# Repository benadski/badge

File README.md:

# Fri3d Camp Badge

Elk zichzelf respecterend hacker/maker/DIY kamp, _moet_ een eigen badge hebben. Zo ook Fri3d Camp :-)

## Concept

Bij het ontwerp van de badge voor Fri3d Camp zijn we vertrokken van drie principes:

1. Een hoge _hack_-baarheid.
2. Leerzaam voor beginners.
3. Interactief.

Daarom brengt de badge het Arduino platform samen met infra-rode stralen om een eenvoudig Fri3d Camp draadloos (IR) netwerk te maken.

Het Arduino platform laat iedereen toe om de software van de badge aan te passen, of er iets totaal anders mee te doen. Naast de badge-functie voor Fri3d Camp, brengen we alle andere mogelijke functionaliteit van de microcontroller naar buiten, zodat de badge, na het kamp, letterlijk kan dienen als jouw eigen Arduino ontwikkel-bord.

Aan de hand van de IR componenten en bijhorende software kunnen de elementaire aspecten van draadloze communicatie uitgelegd worden.

### Meta-Leerzaam

Dit ontwerp is mijn eerste SMD-gebaseerde project en het is op zich al een leerzame ervaring. Daarom bevat deze repository tevens een [design dagboek](design/dagboek.md) waarin ik alle stappen van het proces beschrijf.

## Hardware Design

Twee bestaande projecten kunnen beschouwd worden als de spreekwoordelijke ouders van de badge: 

* [Arduino Pro Micro - 3.3V/8MHz van Sparkfun](https://www.sparkfun.com/products/12587)
* [TV B Gone van Mitch Altman](https://cornfieldelectronics.com/tvbgone/tvbg.home.php)

Voeg nog een IR receiver en een RGB LED toe en je hebt alle basis componenten voor een leerzame, interactieve en zeer _hack_-bare Fri3d Camp badge!

## Software

Om zelf aan de slag te gaan met de [software](src/README.md) zo eenvoudig mogelijk te maken, was één van dé belangrijkste aspecten een makkelijke integratie met het Arduino software platform. De mogelijkheid om de badge te programmeren via de Arduino IDE door middel van louter een micro-USB kabel was daarom een noodzaak.

Om het Arduino platform nog verder zo veel mogelijk te gebruiken, hebben we ook gekozen om zo dicht mogelijk bij een bestaand Arduino bord te blijven en zo is de badge in essentie een [Arduino Mirco](https://www.arduino.cc/en/Main/ArduinoBoardMicro) geworden.

Je kan dus onmiddellijk aan de slag, zoals met elke andere Arduino. Daarnaast bevat deze [repository](src/README.md) enkele applicaties specifiek geschreven voor de Fri3d Camp badge, en dit naast een bibliotheek die het aanspreken van de extras makkelijk maakt. Zo vindt je (weldra) hier:

* dé Fri3d Camp 2016 app
* een implementatie van de TV B Gone applicatie van Mitch Altman
* ...

Als je zelf een nieuwe app maakt die op de Fri3d Camp badge werkt en op een andere, leuke manier gebruik maakt van de IR communicatie en de RGB LED of van andere componenten die je er zelf aan toegevoegd hebt, bezorg ons dan deze code en we voegen ze toe aan deze repository (pull request).

## Credits

De badge werd ontworpen door Christophe VG, samen met de hele Fri3d Camp organisatie, en uitgewerkt met de hulp van Dragan Subotic, Yannick Verbelen, Maarten Weyn, Willy De a Court, Anthony Liekens, Dries Deroeck, Jef Van Den Broeck, Toon Van de Putte,...

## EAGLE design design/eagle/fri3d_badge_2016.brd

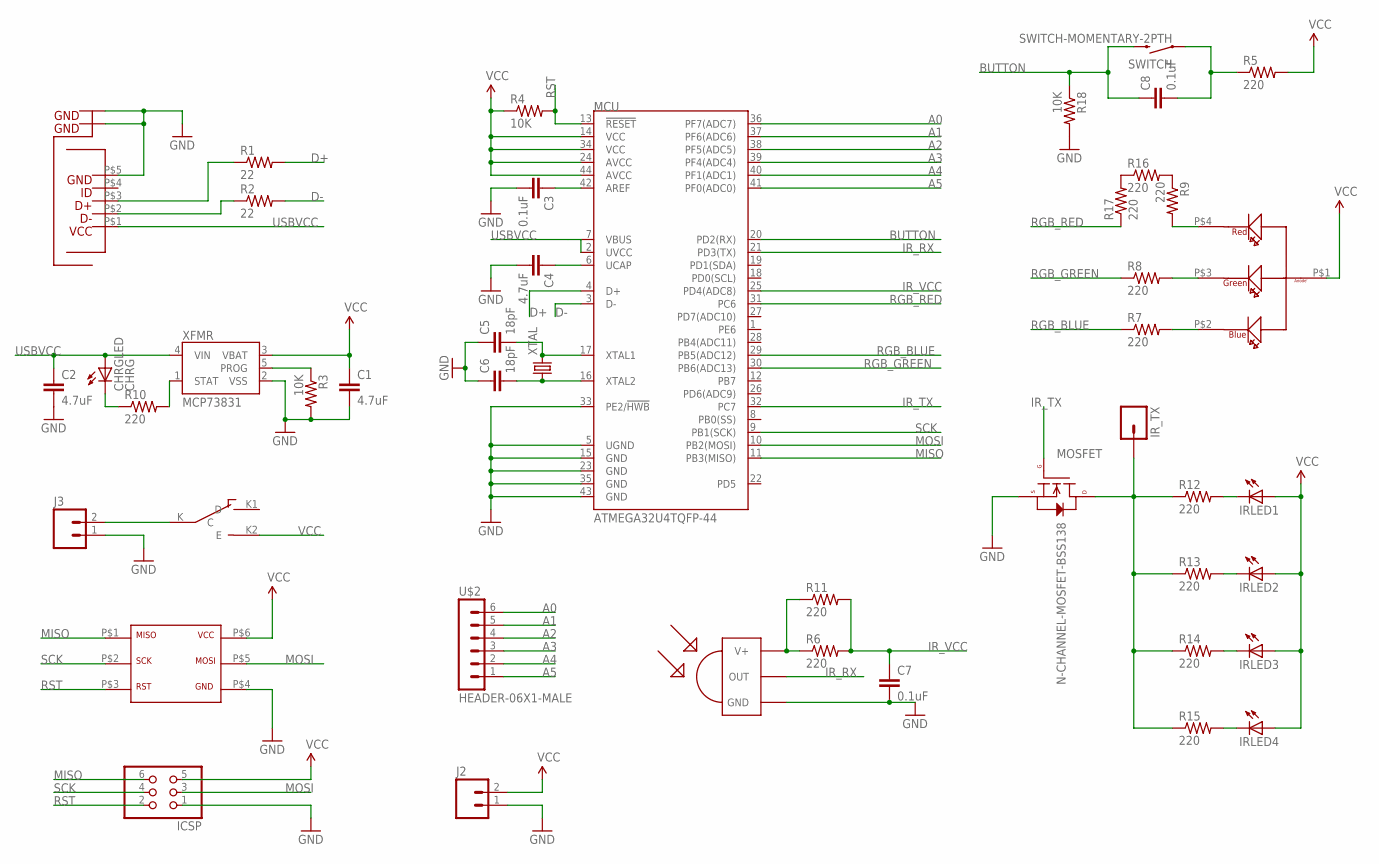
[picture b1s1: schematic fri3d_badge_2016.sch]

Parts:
C1, C2, C4: 4.7uF; 0805
C3, C7, C8: 0.1uF; 0805
C5, C6: 18pF; 0805
CHRGLED: CHRG; CHIPLED_0805
ICSP: PINHD-2X3; 2X03
IRLED1, IRLED2, IRLED3, IRLED4: LEDCHIPLED_0805; CHIPLED_0805
IR_TX: M01PTH; 1X01
J2: M02PTH; 1X02
J3: M02JST-PTH-2; JST-2-PTH
MCU: ATMEGA32U4TQFP-44; TQFP44
MOSFET: N-CHANNEL-MOSFET-BSS138; SOT23-3
R1, R2: 22; 0805
R3, R4, R18: 10K; 0805
R5, R6, R7, R8, R9, R10, R11, R12, R13, R14, R15, R16, R17: 220; 0805
SWITCH: SWITCH-MOMENTARY-2PTH; TACTILE-PTH
U$2: HEADER-06X1-MALE; 06X1-PTH
U$3: TSOP4838; TSOP18XX
U$4: DRAGAN-PERSONAL_AVAGO-RGB-LED
U$5: OCTA-CORE_MCIRO-USB2MOUSER; OCTA-CORE_MICRO-USB2
U$6: SLIDE-SWITCH
U$7: OCTA-CORE_TC2030-IDC
XFMR: MCP73831; SOT23-5
XTAL: CRYSTALHC49S; HC49/S

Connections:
A0: MCU.36 (PF7(ADC7)), U$2.6
A1: MCU.37 (PF6(ADC6)), U$2.5
A2: MCU.38 (PF5(ADC5)), U$2.4
A3: MCU.39 (PF4(ADC4)), U$2.3
A4: MCU.40 (PF1(ADC1)), U$2.2
A5: MCU.41 (PF0(ADC0)), U$2.1
BUTTON: C8.1, MCU.20 (PD2(RX)), R18.1, SWITCH.3 (2)
D+: MCU.4 (D+), R1.2
D-: MCU.3 (D-), R2.2
GND: C1.2, C2.2, C3.2, C4.2, C5.1, C6.1, C7.2, ICSP.1, J2.1, J3.1, MCU.5 (UGND), MCU.15 (GND), MCU.23 (GND), MCU.33 (PE2/!HWB), MCU.35 (GND), MCU.43 (GND), MOSFET.2 (S), R3.2, R18.2, U$3.GND, U$5.P$5, U$5.P$6, U$5.P$7, U$5.P$8, U$5.P$9, U$5.P$10, U$5.P$11, U$5.P$12, U$5.P$13, U$7.P$4, XFMR.2 (VSS)
IR_RX: MCU.21 (PD3(TX)), U$3.OUT
IR_TX: MCU.32 (PC7), MOSFET.1 (G)
IR_VCC: C7.1, MCU.25 (PD4(ADC8)), R6.2, R11.2
MISO: ICSP.6, MCU.11 (PB3(MISO)), U$7.P$1
MOSI: ICSP.3, MCU.10 (PB2(MOSI)), U$7.P$5
unnamed: R2.1, U$5.P$2
unnamed: R1.1, U$5.P$3
unnamed: C8.2, R5.1, SWITCH.1
unnamed: C4.1, MCU.6 (UCAP)
unnamed: R3.1, XFMR.5 (PROG)
unnamed: CHRGLED.C, R10.1
unnamed: C3.1, MCU.42 (AREF)
unnamed: C5.2, MCU.17 (XTAL1), XTAL.2
unnamed: C6.2, MCU.16 (XTAL2), XTAL.1
unnamed: R6.1, R11.1, U$3.VCC (V+)
unnamed: R9.1, R16.2
unnamed: R16.1, R17.2
unnamed: IRLED1.C, R12.2
unnamed: IRLED2.C, R13.2
unnamed: IRLED3.C, R14.2
unnamed: IRLED4.C, R15.2
unnamed: J3.2, U$6.K (C)
unnamed: R9.2, U$4.P$4
unnamed: R8.2, U$4.P$3
unnamed: R7.2, U$4.P$2
unnamed: R10.2, XFMR.1 (STAT)
unnamed: IR_TX.1, MOSFET.3 (D), R12.1, R13.1, R14.1, R15.1
RGB_BLUE: MCU.29 (PB5(ADC12)), R7.1
RGB_GREEN: MCU.30 (PB6(ADC13)), R8.1
RGB_RED: MCU.31 (PC6), R17.1
RST: ICSP.2, MCU.13 (!RESET), R4.2, U$7.P$3
SCK: ICSP.4, MCU.9 (PB1(SCK)), U$7.P$2
USBVCC: C2.1, CHRGLED.A, MCU.2 (UVCC), MCU.7 (VBUS), U$5.P$1, XFMR.4 (VIN)
VCC: C1.1, ICSP.5, IRLED1.A, IRLED2.A, IRLED3.A, IRLED4.A, J2.2, MCU.14 (VCC), MCU.24 (AVCC), MCU.34 (VCC), MCU.44 (AVCC), R4.1, R5.2, U$4.P$1, U$6.K2 (E), U$7.P$6, XFMR.3 (VBAT)

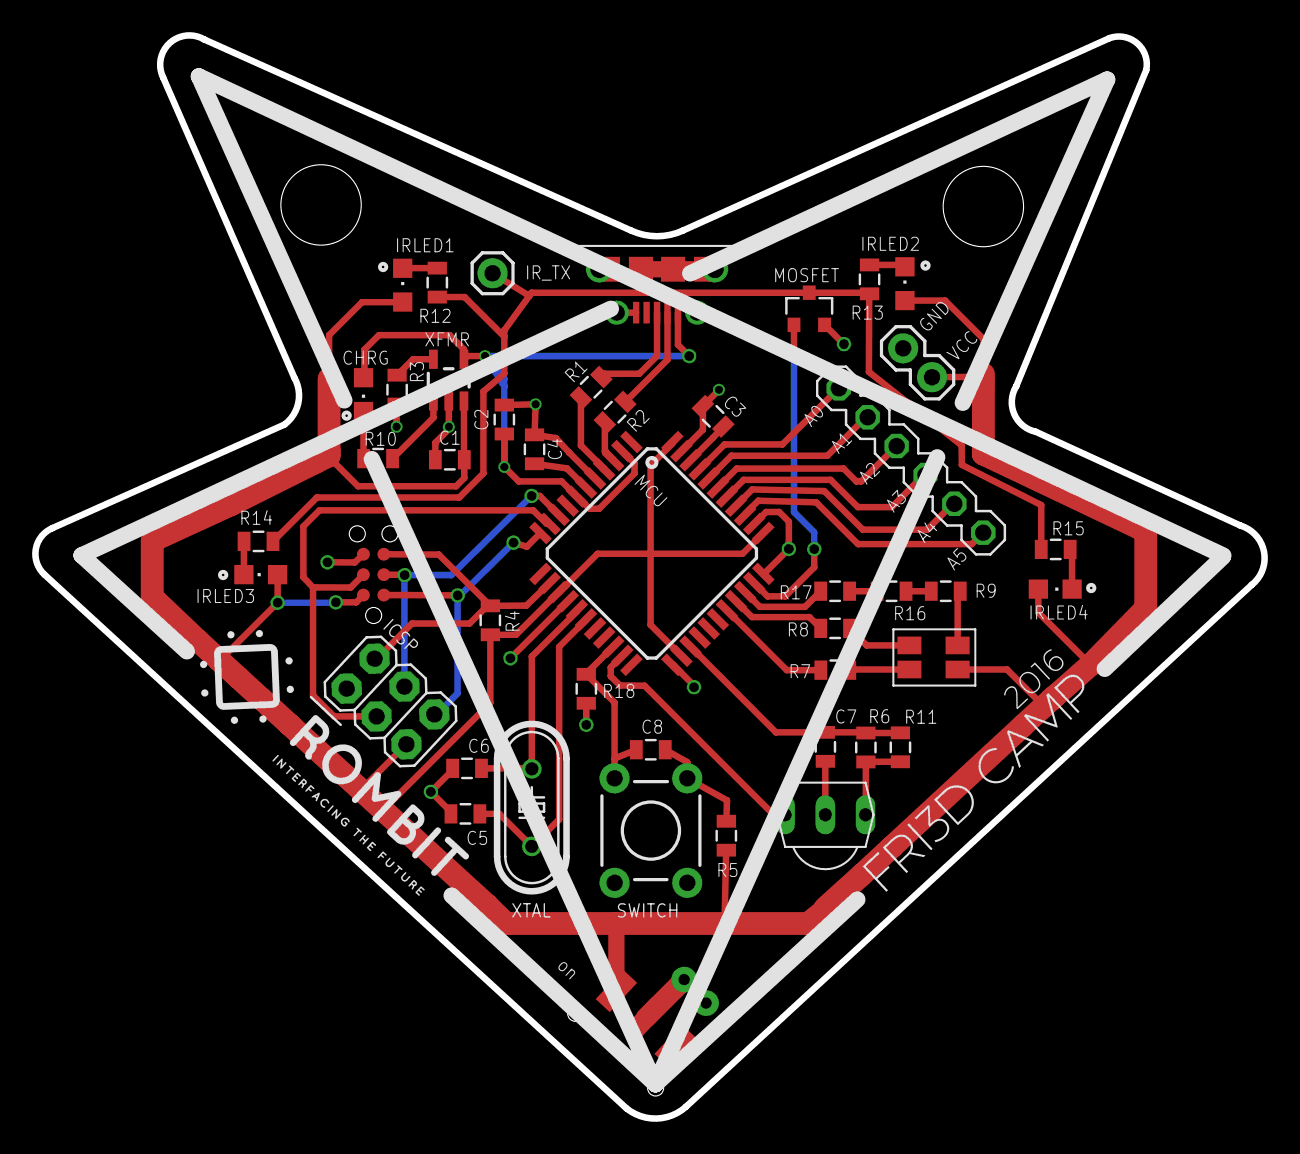
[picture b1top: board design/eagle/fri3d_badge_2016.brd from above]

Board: 2 copper layers, 76.5 x 67.4 mm, 46 parts (1 on the bottom side), 44 nets.

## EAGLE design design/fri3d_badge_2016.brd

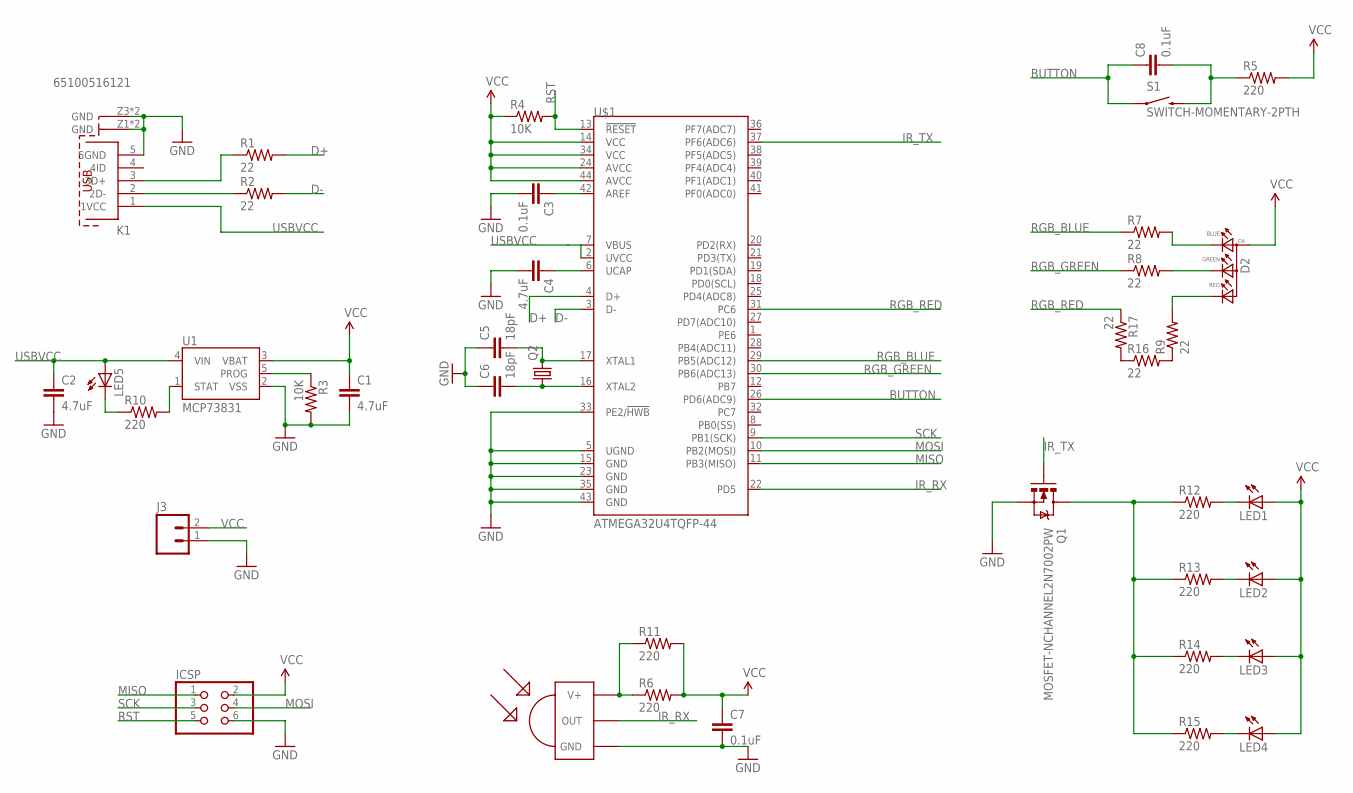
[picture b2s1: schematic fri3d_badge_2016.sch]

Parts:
C1, C2, C4: 4.7uF; 0805
C3, C7, C8: 0.1uF; 0805
C5, C6: 18pF; 0805
D2: 0.13_RGB_LEDPLCC; P-LCC-4-3
ICSP: PINHD-2X3; 2X03
J3: M02JST-PTH-VERT; JST-2-PTH-VERT
K1: 65100516121
LED1, LED2, LED3, LED4, LED5: LEDCHIPLED_0805; CHIPLED_0805
Q1: MOSFET-NCHANNEL2N7002PW; SOT323
Q2: CRYSTALHC49S; HC49/S
R1, R2, R7, R8, R9, R16, R17: 22; 0805
R3, R4: 10K; 0805
R5, R6, R10, R11, R12, R13, R14, R15: 220; 0805
S1: SWITCH-MOMENTARY-2PTH; TACTILE-PTH
U1: MCP73831; SOT23-5
U$1: ATMEGA32U4TQFP-44; TQFP44
U$3: TSOP4838; TSOP18XX

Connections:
BUTTON: C8.1, S1.1, U$1.26 (PD6(ADC9))
D+: R1.2, U$1.4 (D+)
D-: R2.2, U$1.3 (D-)
GND: C1.2, C2.2, C3.2, C4.2, C5.1, C6.1, C7.2, ICSP.6, J3.1, K1.5 (5GND), K1.Z1 (GND), K1.Z2 (GND), K1.Z3 (GND), K1.Z4 (GND), Q1.2 (S), R3.2, U1.2 (VSS), U$1.5 (UGND), U$1.15 (GND), U$1.23 (GND), U$1.33 (PE2/!HWB), U$1.35 (GND), U$1.43 (GND), U$3.GND
IR_RX: U$1.22 (PD5), U$3.OUT
IR_TX: Q1.1 (G), U$1.18 (PD0(SCL)), U$1.37 (PF6(ADC6))
MISO: ICSP.1, U$1.11 (PB3(MISO))
MOSI: ICSP.4, U$1.10 (PB2(MOSI))
unnamed: K1.2 (2D-), R2.1
unnamed: K1.3 (3D+), R1.1
unnamed: C8.2, R5.1, S1.3 (2)
unnamed: C4.1, U$1.6 (UCAP)
unnamed: R3.1, U1.5 (PROG)
unnamed: LED5.C, R10.1
unnamed: C3.1, U$1.42 (AREF)
unnamed: C5.2, Q2.2, U$1.17 (XTAL1)
unnamed: C6.2, Q2.1, U$1.16 (XTAL2)
unnamed: R6.1, R11.1, U$3.VCC (V+)
unnamed: R9.1, R16.2
unnamed: R16.1, R17.2
unnamed: LED1.C, R12.2
unnamed: LED2.C, R13.2
unnamed: LED3.C, R14.2
unnamed: LED4.C, R15.2
unnamed: D2.3 (BLUE), R7.2
unnamed: D2.2 (GREEN), R8.2
unnamed: D2.1 (RED), R9.2
unnamed: R10.2, U1.1 (STAT)
unnamed: Q1.3 (D), R12.1, R13.1, R14.1, R15.1
RGB_BLUE: R7.1, U$1.29 (PB5(ADC12))
RGB_GREEN: R8.1, U$1.30 (PB6(ADC13))
RGB_RED: R17.1, U$1.31 (PC6)
RST: ICSP.5, R4.2, U$1.13 (!RESET)
SCK: ICSP.3, U$1.9 (PB1(SCK))
USBVCC: C2.1, K1.1 (1VCC), LED5.A, U1.4 (VIN), U$1.2 (UVCC), U$1.7 (VBUS)
VCC: C1.1, C7.1, D2.4 (ANODE), ICSP.2, J3.2, LED1.A, LED2.A, LED3.A, LED4.A, R4.1, R5.2, R6.2, R11.2, U1.3 (VBAT), U$1.14 (VCC), U$1.24 (AVCC), U$1.34 (VCC), U$1.44 (AVCC)

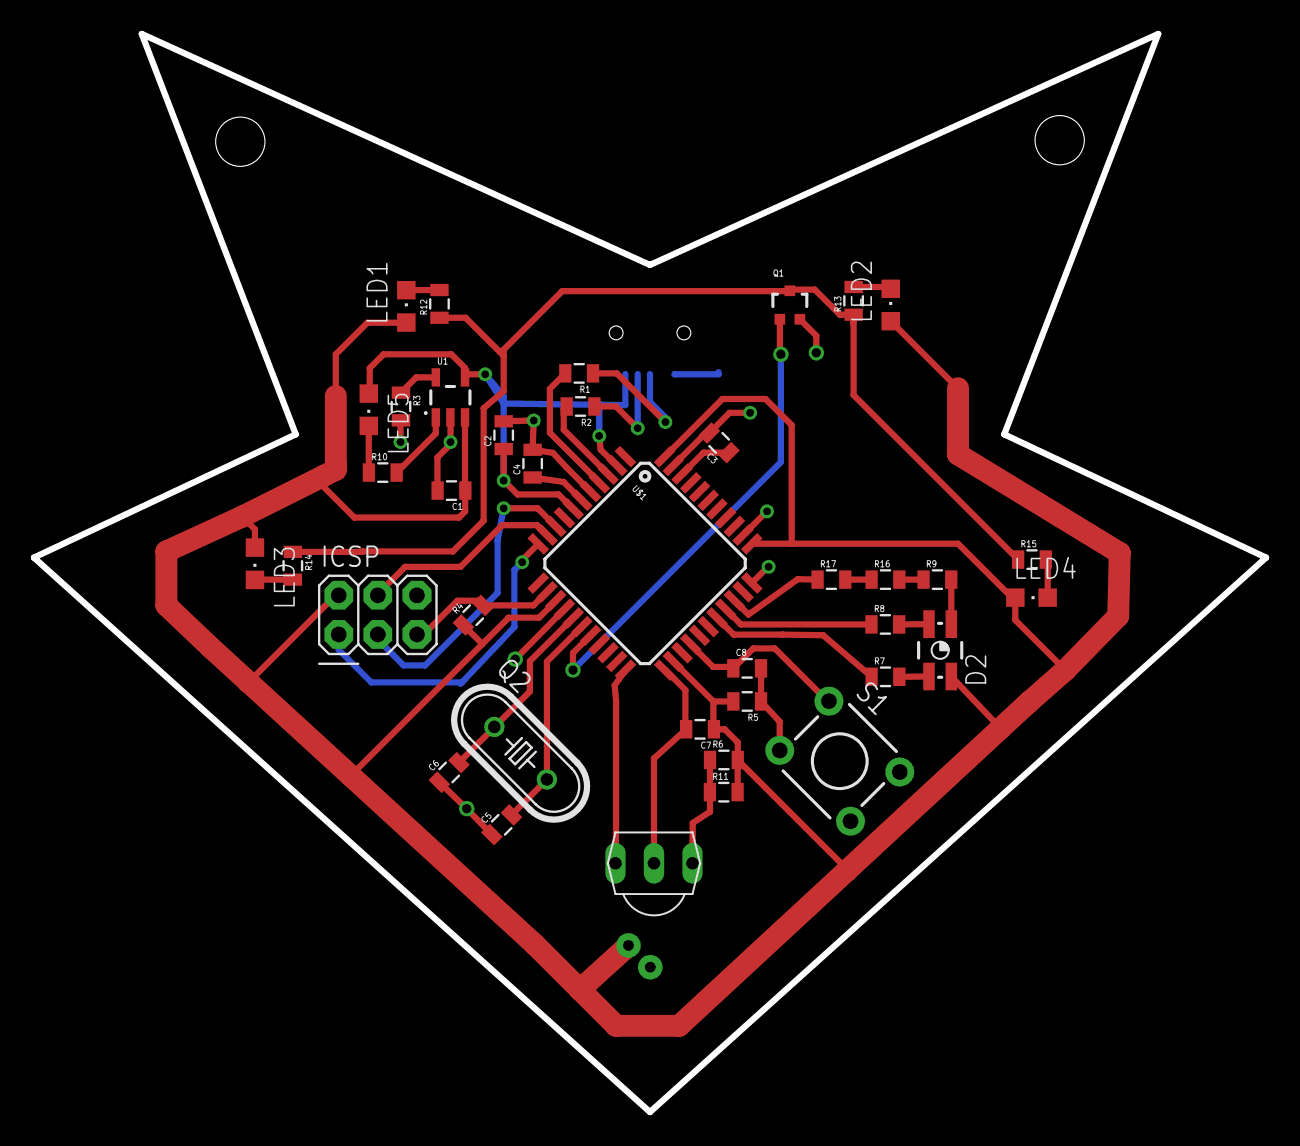
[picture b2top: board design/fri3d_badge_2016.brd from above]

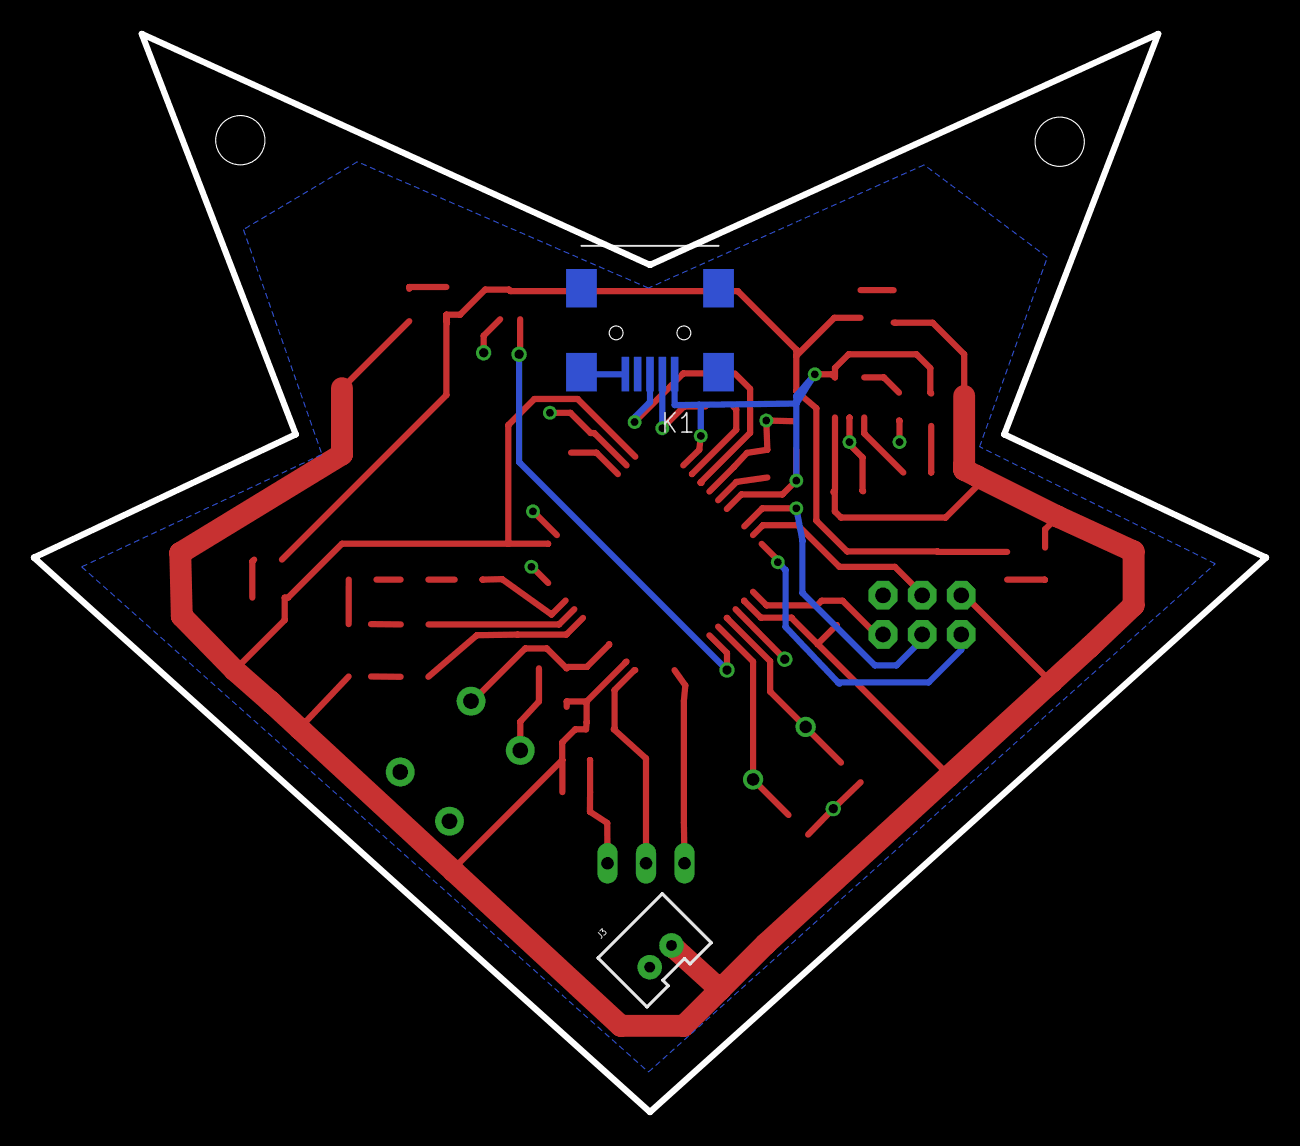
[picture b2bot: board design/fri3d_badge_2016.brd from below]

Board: 2 copper layers, 80.0 x 70.0 mm, 40 parts (2 on the bottom side), 36 nets.

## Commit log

2016-03-14 initial repo setup
2016-03-14 added concept
2016-03-14 added credits section
2016-03-14 added references to other project sources
2016-03-14 added initial/draft schematic design
2016-03-14 ignoring Eagle backup & lock files
2016-03-15 added missing cap+resistor on IR Receiver
2016-03-16 update of design based on feedback by Dragan
2016-03-16 little more documentation (mostly stubs)
2016-03-18 ignore Mac artefacts
2016-03-18 added resistors for IR LEDs
2016-03-18 documented first steps in design diary
2016-04-13 update to version 2 of design
2016-04-16 added board design, outline and initial placing
2016-05-19 created first version (draft) PCB layout
2016-05-23 layout tweaks -> v2
2016-05-23 added more datasheets
2016-05-29 added bootloader
2016-05-29 added TV B Fri3d
2016-05-29 added Alive sketch
2016-05-29 updated README: contributors, ref to software
2016-05-29 added index README for src/ folder
2016-05-29 replacing wrong world codes file
2016-05-29 fixed wrongly connected IR LED net
2016-05-29 ignoring gerber output files
2016-05-31 moved eagle files in project folder
2016-05-31 added RGB example
2016-05-31 added datasheet for RGB LED
2016-06-04 first step towards the Fri3dBadge library
2016-06-04 added button support + example
2016-06-04 added PCB layout v1
2016-06-05 added header for Analog pins A0-5
2016-06-05 fixed IR receiver and button Arduino pins
2016-06-05 added switch and draft silkscreen
2016-06-05 changed resistors on RGB LED to 220 (to test)
2016-06-06 fixed RGB LED footprint (+draft silk)
2016-06-06 fixed USB connector (Mouser)
2016-06-06 fixed switch footprint
2016-06-06 replaced ICSP header with Tag Connect pads
2016-06-06 fixed DRC issues
2016-06-06 cleaned up silk
2016-06-06 redid Tag Connect mapping (same layout)
2016-06-06 added Arduino pin mapping + Tag Connect Datasheet
2016-06-07 added first stab at sponsor logo
2016-06-12 removed redundant layout screenshot
2016-06-12 added silkscreen generation files
2016-06-12 added Fri3d Camp 2016 logo + silkscreen clean up
2016-06-19 updated pin for button to correct (new) one
2016-06-21 added interrupt driven button change handling
2016-06-21 initialise RGB LED to black
2016-06-21 added support for going to sleep… deeply ;-)
2016-06-22 IR powered by pin, added headers, cleaned up silk
2016-06-22 added support for sleep_for(sec) using watchdog
2016-06-24 attached IR/MOSFET to correct pin for IRremote
2016-07-04 fixed MOSFET footprint + added dots for diodes
2016-07-04 added header for IR_TX
2016-07-04 added mounting ULP export script + initial config
2016-07-04 fixed incorrect MOSFET footprint
2016-07-06 removed not-placed components, added RGB LED
2016-07-10 moved IR_TX test header
2016-07-10 implemented draft fading example
2016-07-10 added IR ping-pong
2016-07-11 final silkscreen touch-ups
2016-07-11 fixed bad font on backside
2016-08-06 renamed license/ to info/ for case-insensitive FSs
2016-08-06 added failure override for avrdude fails on locks
2016-08-06 improved wait text in between boot loader flashes
2016-08-08 removed old IR test code
2016-08-08 implemented camp app
2016-08-08 fixed whitespace/tab typo
2016-08-09 some documentation updates
2016-08-09 removed unused Serial
2016-08-09 added comment about millis() rollover ;-)
2016-08-09 fixed (really) too small random INTERVAL part
2016-08-13 Camp badge software with more RGB reply effects!
2016-08-13 Camp badge software with more RGB reply effects!
    Fri3d kleurtjes erbij!
2016-08-13 Camp badge software with more RGB reply effects!
    More startup colors, alternative fadeout
2016-08-14 Camp badge software with more RGB reply effects!
    Better IR lib and range. Also sends random IR sequences (RC-5?)
2016-08-14 Create Fri3dBadge_IR.cpp
    Closer to 38kHz, but not quite.
2016-08-14 Rename camp_more_effects to camp_more_effects.ino
2016-08-14 Create Fri3dBadge_IR.h
    Niets gewijzigd

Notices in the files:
parts and their libraries:
SparkFun-Capacitors: Licensing: Creative Commons ShareAlike 4.0 International - https://creativecommons.org/licenses/by-sa/4.0
Input-Output_Connectors_rev15d: Copyright: Würth Elektronik
